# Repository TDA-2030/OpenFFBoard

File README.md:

# OpenFFBoard-ESP32S2 + VESC

这里将介绍使用 ESP32-S2/S3 版本的 OpenFFBoard 搭配自制 VESC 驱动器使用的一个低成本实现直驱力反馈方向盘方案。[OpenffBoard](https://github.com/Ultrawipf/OpenFFBoard) 是一个开源的力反馈方向盘的项目，整个项目硬件分为 `控制板` 和 `电机驱动板` 两个部分，这里对两个部分都进行了低成本方向的修改。

## 文件结构

```
├── LICENSE                <- 开源协议 >
├── Simple-BLDC            <- 电机驱动板 >
├── openffboard-esp32s2    <- OpenFFBoard 主控板 >
├── Structural_parts       <- 一些可能有帮助的结构件>
└── README.md              <- 此文件 >
```

## OpenFFBoard-ESP32S2 控制板

原项目控制板是 STM32F4 做主控，这里将主控换成了[乐鑫](https://www.espressif.com/zh-hans)的 ESP32-S2/S3 芯片，成本得到极大的降低，同时提供了 WiFi 的连接能力（虽然现在并没有用上）。硬件开源资料见 [openffboard-esp32s2](./openffboard-esp32s2)

> V1.1 版本的硬件支持 ESP32-S2 和 ESP32-S3 二选一焊接，下文统称为 ESP32

和原项目相比，ESP32 不能提供足够多的 GPIO ，所以按键输入和模拟输入通道数均从原来的 8 通道精简到了 4 通道。详细信息见原理图 [esp32s2-openffb.pdf](openffboard-esp32s2/esp32s2-openffb.pdf)。
ESP32 控制板的源码已提交 Pull Request 到原项目，支持的功能以及进度见 [PR](https://github.com/Ultrawipf/OpenFFBoard/pull/46)。

### 控制板固件烧录

参见[快速下载固件指南](https://github.com/TDA-2030/OpenFFBoard/tree/feature/add_esp32s2/Firmware/Targets/ESP32SX#quick-download-firmware)

## 电机驱动板

为了造福广大劳动人民，针对原项目的电机驱动我也进行了低成本的改造，原项目是采用了比较贵的 TMC4761 专用 FOC 控制芯片，我将著名的开源电调 [VESC](https://vesc-project.com/) 进行了魔改，去掉了昂贵的 DRV8301 芯片，用多个芯片实现了这一个芯片的功能。集成度下降了，但是价格更友好。魔改后的 VESC 我叫它 `Simple-BLDC` 。关于电机驱动板的更多信息见 [Simple-BLDC](Simple-BLDC/README.md)

## 组装好的样子

## 测试工具

[WheelTest](./WheelTest.rar) 提供了一个测试力反馈功能是否正常的软件

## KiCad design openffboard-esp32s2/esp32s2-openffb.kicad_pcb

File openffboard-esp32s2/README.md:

## Preview image

## Known issues

The silk screen of the two buttons is wrong

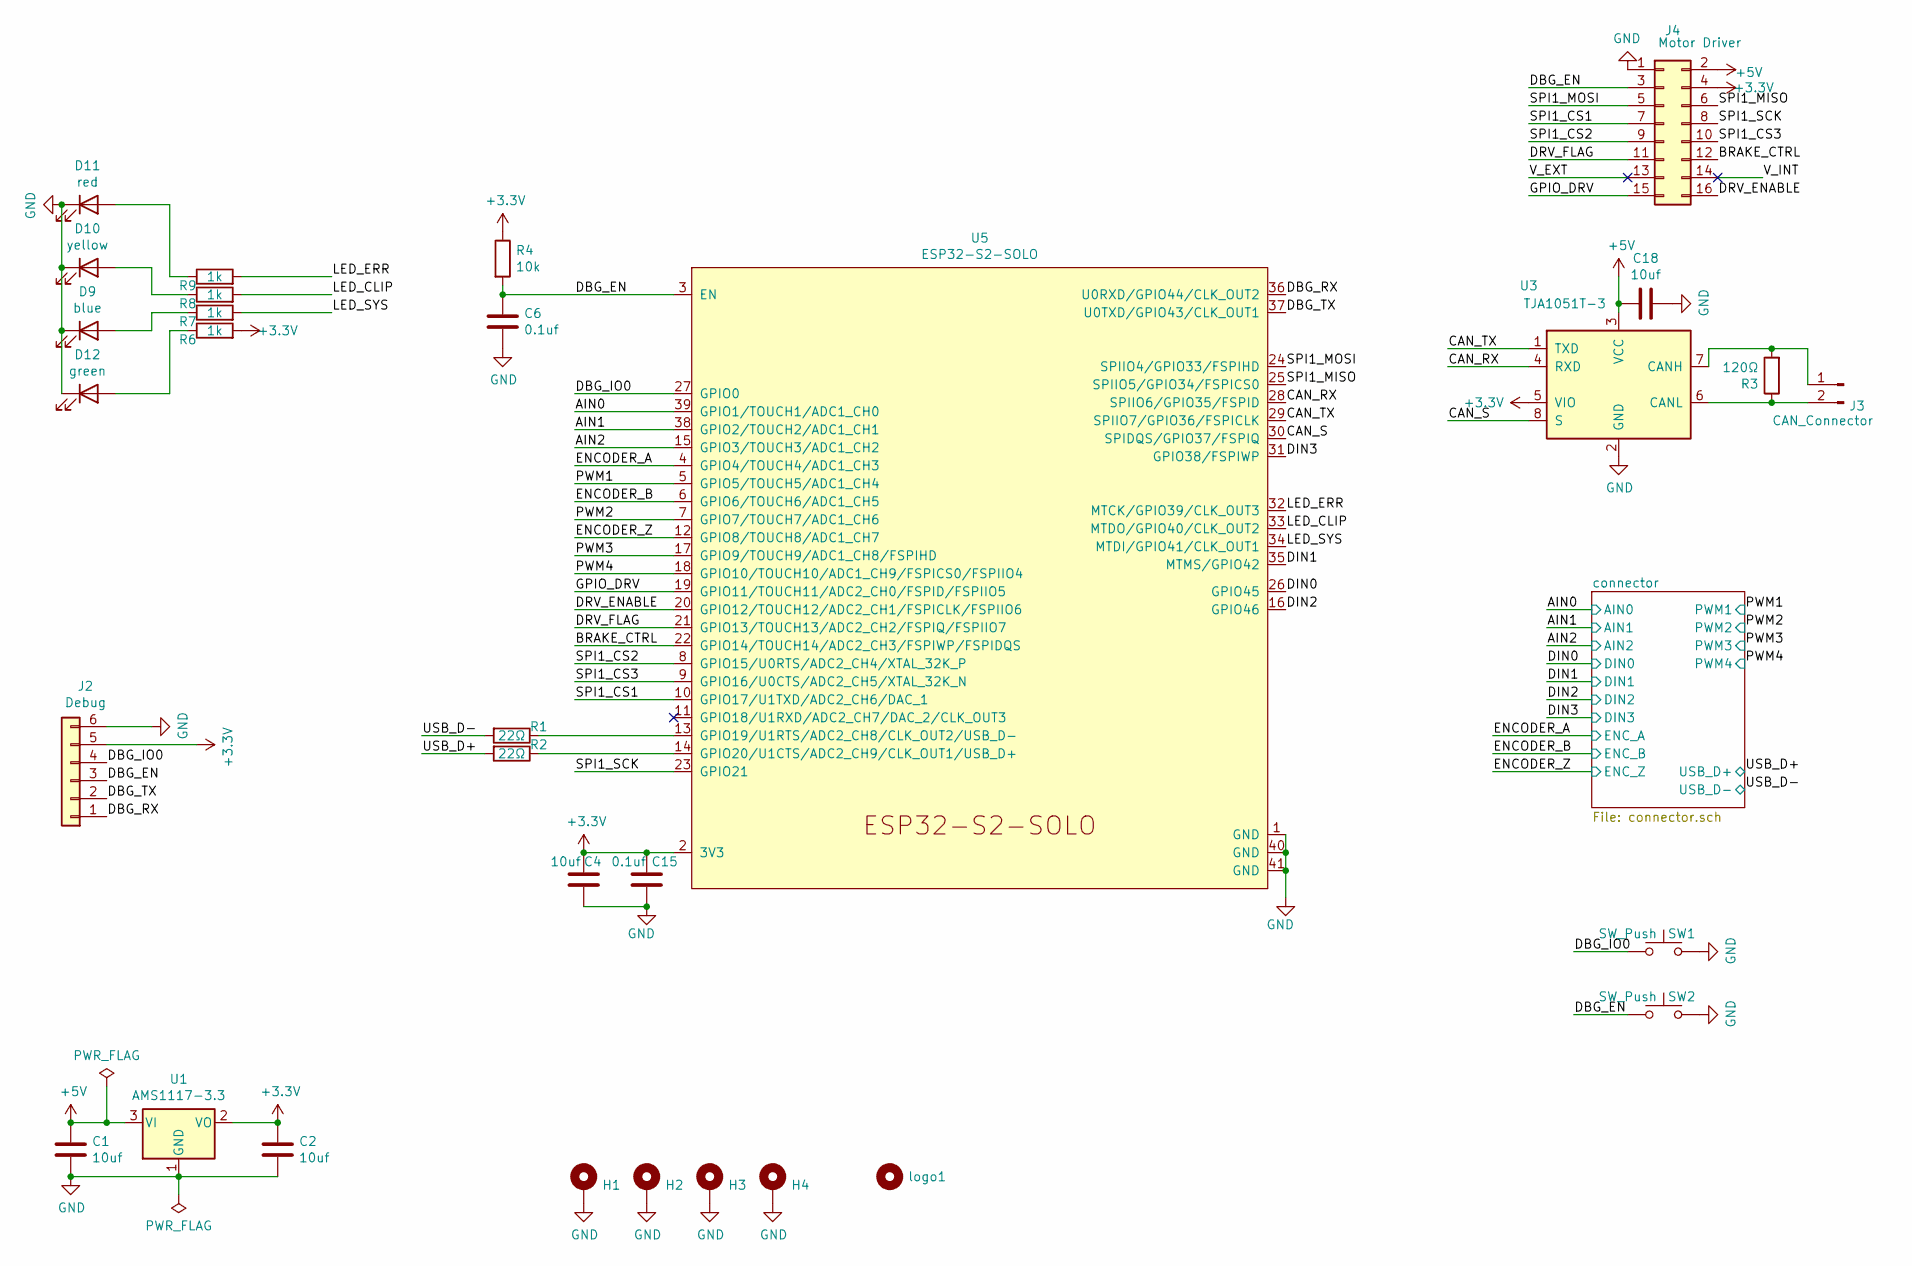
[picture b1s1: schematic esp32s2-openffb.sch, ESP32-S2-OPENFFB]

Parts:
C1, C2, C4, C18: 10uf; C_0603_1608Metric
C6, C15: 0.1uf; C_0402_1005Metric
D9: blue; LED_0603_1608Metric
D10: yellow; LED_0603_1608Metric
D11: red; LED_0603_1608Metric
D12: green; LED_0603_1608Metric
H1, H2, H3, H4: MountingHole_Pad; MountingHole_3.2mm_M3_Pad_Via
J2: Debug; PinHeader_1x06_P2.54mm_Vertical
J3: CAN_Connector; PinHeader_1x02_P2.54mm_Vertical
J4: Motor Driver; PinHeader_2x08_P2.54mm_Vertical
R1, R2: 22Ω; R_0402_1005Metric
R3: 120Ω; R_0603_1608Metric
R4: 10k; R_0402_1005Metric
R6, R7, R8, R9: 1k; R_0402_1005Metric
SW1, SW2: SW_Push; SW_SPST_EVPBF
U1: AMS1117-3.3; SOT-223-3_TabPin2
U3: TJA1051T-3; SOIC-8_3.9x4.9mm_P1.27mm
U5: ESP32-S2-SOLO
logo1: logo; OSHW-Logo2_9.8x8mm_SilkScreen

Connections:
+3V3: C2.2, C4.1, C15.1, J2.5, J4.4, R4.1, R6.2, U1.2 (VO), U3.5 (VIO), U5.2 (3V3); also elsewhere on the board
+5V: C1.2, C18.2, J4.2, U1.3 (VI), U3.3 (VCC); also elsewhere on the board
/AIN0: U5.39 (GPIO1/TOUCH1/ADC1_CH0); also elsewhere on the board
/AIN1: U5.38 (GPIO2/TOUCH2/ADC1_CH1); also elsewhere on the board
/AIN2: U5.15 (GPIO3/TOUCH3/ADC1_CH2); also elsewhere on the board
/BRAKE_CTRL: J4.12, U5.22 (GPIO14/TOUCH14/ADC2_CH3/FSPIWP/FSPIDQS)
/CAN_RX: U3.4 (RXD), U5.28 (SPIIO6/GPIO35/FSPID)
/CAN_S: U3.8 (S), U5.30 (SPIDQS/GPIO37/FSPIQ)
/CAN_TX: U3.1 (TXD), U5.29 (SPIIO7/GPIO36/FSPICLK)
/DBG_EN: C6.1, J2.3, J4.3, R4.2, SW2.1, U5.3 (EN)
/DBG_IO0: J2.4, SW1.1, U5.27 (GPIO0)
/DBG_RX: J2.1, U5.36 (U0RXD/GPIO44/CLK_OUT2)
/DBG_TX: J2.2, U5.37 (U0TXD/GPIO43/CLK_OUT1)
/DIN0: U5.26 (GPIO45); also elsewhere on the board
/DIN1: U5.35 (MTMS/GPIO42); also elsewhere on the board
/DIN2: U5.16 (GPIO46); also elsewhere on the board
/DIN3: U5.31 (GPIO38/FSPIWP); also elsewhere on the board
/DRV_ENABLE: J4.16, U5.20 (GPIO12/TOUCH12/ADC2_CH1/FSPICLK/FSPIIO6)
/DRV_FLAG: J4.11, U5.21 (GPIO13/TOUCH13/ADC2_CH2/FSPIQ/FSPIIO7)
/ENCODER_A: U5.4 (GPIO4/TOUCH4/ADC1_CH3); also elsewhere on the board
/ENCODER_B: U5.6 (GPIO6/TOUCH6/ADC1_CH5); also elsewhere on the board
/ENCODER_Z: U5.12 (GPIO8/TOUCH8/ADC1_CH7); also elsewhere on the board
/GPIO_DRV: J4.15, U5.19 (GPIO11/TOUCH11/ADC2_CH0/FSPID/FSPIIO5)
/LED_CLIP: R8.2, U5.33 (MTDO/GPIO40/CLK_OUT2)
/LED_ERR: R9.2, U5.32 (MTCK/GPIO39/CLK_OUT3)
/LED_SYS: R7.2, U5.34 (MTDI/GPIO41/CLK_OUT1)
/PWM1: U5.5 (GPIO5/TOUCH5/ADC1_CH4); also elsewhere on the board
/PWM2: U5.7 (GPIO7/TOUCH7/ADC1_CH6); also elsewhere on the board
/PWM3: U5.17 (GPIO9/TOUCH9/ADC1_CH8/FSPIHD); also elsewhere on the board
/PWM4: U5.18 (GPIO10/TOUCH10/ADC1_CH9/FSPICS0/FSPIIO4); also elsewhere on the board
/SPI1_CS1: J4.7, U5.10 (GPIO17/U1TXD/ADC2_CH6/DAC_1)
/SPI1_CS2: J4.9, U5.8 (GPIO15/U0RTS/ADC2_CH4/XTAL_32K_P)
/SPI1_CS3: J4.10, U5.9 (GPIO16/U0CTS/ADC2_CH5/XTAL_32K_N)
/SPI1_MISO: J4.6, U5.25 (SPIIO5/GPIO34/FSPICS0)
/SPI1_MOSI: J4.5, U5.24 (SPIIO4/GPIO33/FSPIHD)
/SPI1_SCK: J4.8, U5.23 (GPIO21)
/USB_D+: R2.2; also elsewhere on the board
/USB_D-: R1.2; also elsewhere on the board
GND: C1.1, C2.1, C4.2, C6.2, C15.2, C18.1, D9.1 (K), D10.1 (K), D11.1 (K), D12.1 (K), H1.1, H2.1, H3.1, H4.1, J2.6, J4.1, SW1.2, SW2.2, U1.1 (GND), U3.2 (GND), U5.1 (GND), U5.40 (GND), U5.41 (GND); also elsewhere on the board
unnamed: D9.2 (A), R7.1
unnamed: D10.2 (A), R8.1
unnamed: D11.2 (A), R9.1
unnamed: D12.2 (A), R6.1
unnamed: J3.1, R3.2, U3.7 (CANH)
unnamed: J3.2, R3.1, U3.6 (CANL)
unnamed: R1.1, U5.13 (GPIO19/U1RTS/ADC2_CH8/CLK_OUT2/USB_D-)
unnamed: R2.1, U5.14 (GPIO20/U1CTS/ADC2_CH9/CLK_OUT1/USB_D+)

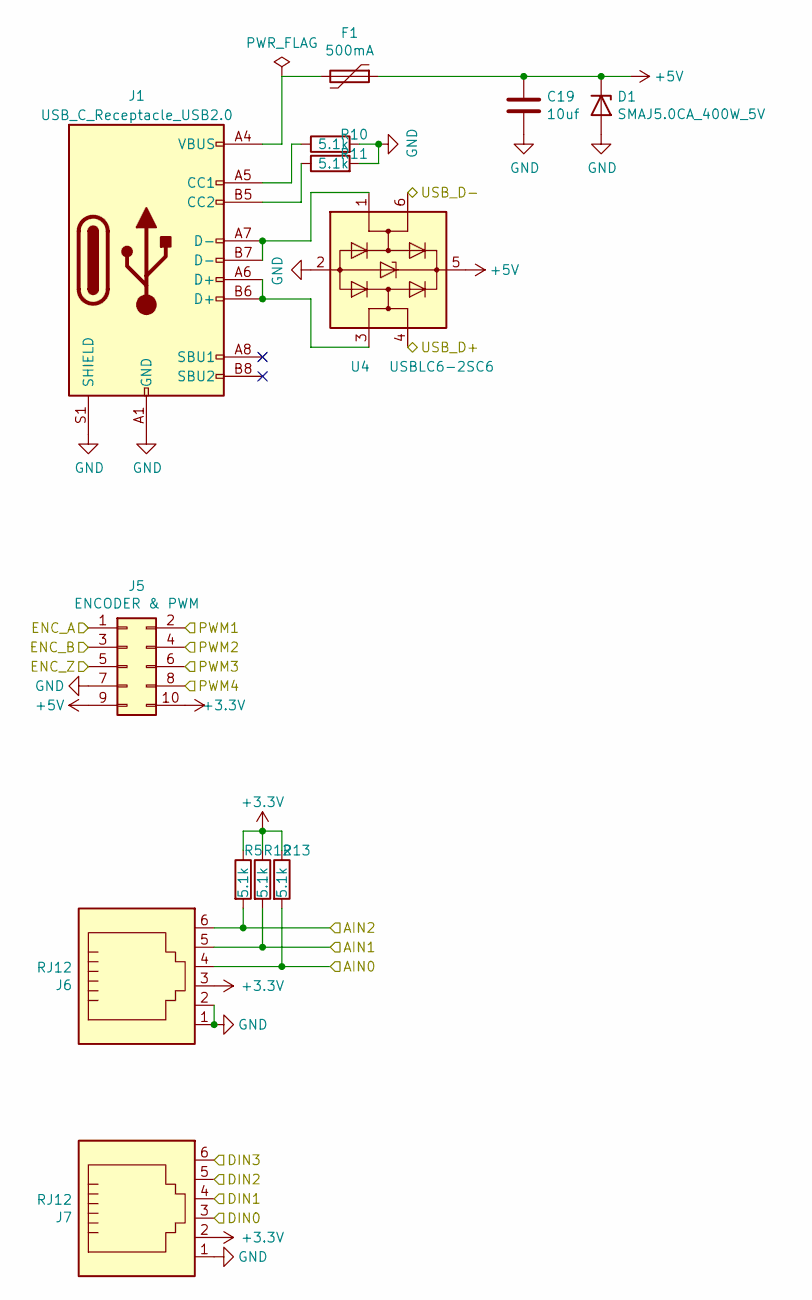
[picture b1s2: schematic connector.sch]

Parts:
C19: 10uf; C_0603_1608Metric
D1: SMAJ5.0CA_400W_5V; D_SMA
F1: 500mA; Fuse_0805_2012Metric
J1: USB_C_Receptacle_USB2.0; USB_C_Receptacle_Palconn_UTC16-G
J5: ENCODER & PWM; PinHeader_2x05_P2.54mm_Vertical
J6, J7: RJ12; RJ25_Wayconn_MJEA-660X1_Horizontal
R5, R10, R11, R12, R13: 5.1k; R_0402_1005Metric
U4: USBLC6-2SC6; SOT-23-6

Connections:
+3V3: J5.10, J6.3, J7.2, R5.1, R12.1, R13.1; also elsewhere on the board
+5V: C19.2, D1.1 (A1), F1.1, J5.9, U4.5 (VBUS); also elsewhere on the board
/AIN0: J6.4, R13.2; also elsewhere on the board
/AIN1: J6.5, R12.2; also elsewhere on the board
/AIN2: J6.6, R5.2; also elsewhere on the board
/DIN0: J7.3; also elsewhere on the board
/DIN1: J7.4; also elsewhere on the board
/DIN2: J7.5; also elsewhere on the board
/DIN3: J7.6; also elsewhere on the board
/ENCODER_A: J5.1; also elsewhere on the board
/ENCODER_B: J5.3; also elsewhere on the board
/ENCODER_Z: J5.5; also elsewhere on the board
/PWM1: J5.2; also elsewhere on the board
/PWM2: J5.4; also elsewhere on the board
/PWM3: J5.6; also elsewhere on the board
/PWM4: J5.8; also elsewhere on the board
/USB_D+: U4.4 (I/O2); also elsewhere on the board
/USB_D-: U4.6 (I/O1); also elsewhere on the board
GND: C19.1, D1.2 (A2), J1.A1 (GND), J1.A12 (GND), J1.B1 (GND), J1.B12 (GND), J1.S1 (SHIELD), J5.7, J6.1, J6.2, J7.1, R10.2, R11.2, U4.2 (GND); also elsewhere on the board
unnamed: F1.2, J1.A4 (VBUS), J1.A9 (VBUS), J1.B4 (VBUS), J1.B9 (VBUS)
unnamed: J1.A5 (CC1), R10.1
unnamed: J1.A6 (D+), J1.B6 (D+), U4.3 (I/O2)
unnamed: J1.A7 (D-), J1.B7 (D-), U4.1 (I/O1)
unnamed: J1.B5 (CC2), R11.1

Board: 2 copper layers, 44 parts (0 on the bottom side), 52 nets, no tracks yet.

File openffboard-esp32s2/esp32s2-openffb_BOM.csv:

"Comment","Description","Designator","Footprint","LibRef","Pins","Quantity","PartNumber","url",
"10uf","desc","C1,C2,C3,C4,C19,","C_0603_1608Metric","libref","2","5","","",
"0.1uf","desc","C6,C15,","C_0402_1005Metric","libref","2","2","","",
"SMAJ5.0CA_400W_5V","desc","D1,","D_SMA","libref","2","1","","",
"blue","desc","D9,","LED_0603_1608Metric","libref","2","1","","",
"yellow","desc","D10,","LED_0603_1608Metric","libref","2","1","","",
"red","desc","D11,","LED_0603_1608Metric","libref","2","1","","",
"green","desc","D12,","LED_0603_1608Metric","libref","2","1","","",
"500mA","desc","F1,","Fuse_0805_2012Metric","libref","2","1","","",
"22Ω","desc","R1,R2,","R_0402_1005Metric","libref","2","2","","",
"10k","desc","R4,","R_0402_1005Metric","libref","2","1","","",
"5.1k","desc","R5,R10,R11,R12,R13,","R_0402_1005Metric","libref","2","5","","",
"1k","desc","R6,R7,R8,R9,","R_0402_1005Metric","libref","2","4","","",
"120Ω","desc","R15,","R_0603_1608Metric","libref","2","1","","",
"AMS1117-3.3","desc","U1,","SOT-223-3_TabPin2","libref","4","1","","",
"ESP32-S3-WROOM-1","desc","U2,","ESP32-S3-WROOM-1","libref","49","1","","",
"TJA1051T-3","desc","U3,","SOIC-8_3.9x4.9mm_P1.27mm","libref","8","1","","",
"USBLC6-2SC6","desc","U4,","SOT-23-6","libref","6","1","","",
"ESP32-S2-SOLO","desc","U5,","ESP32-S2-SOLO","libref","49","1","","",
"SW_Push","desc","SW1,SW2,","SW_SPST_EVPBF","libref","4","2","","",
"logo","desc","logo1,","OSHW-Logo2_9.8x8mm_SilkScreen","libref","0","1","","",
"Through Hole Items ",
"MountingHole_Pad","desc","H1,H2,H3,H4,","MountingHole_3.2mm_M3_Pad_Via","libref","9","4","","",
"USB_C_Receptacle_USB2.0","desc","J1,","USB_C_Receptacle_Palconn_UTC16-G","libref","22","1","","",
"Debug","desc","J2,","PinHeader_1x06_P2.54mm_Vertical","libref","6","1","","",
"CAN_Connector","desc","J3,","PinHeader_1x02_P2.54mm_Vertical","libref","2","1","","",
"Motor Driver","desc","J4,","PinHeader_2x08_P2.54mm_Vertical","libref","16","1","","",
"ENCODER & PWM","desc","J5,","PinHeader_2x05_P2.54mm_Vertical","libref","10","1","","",
"RJ12","desc","J6,J7,","RJ25_Wayconn_MJEA-660X1_Horizontal","libref","8","2","","",

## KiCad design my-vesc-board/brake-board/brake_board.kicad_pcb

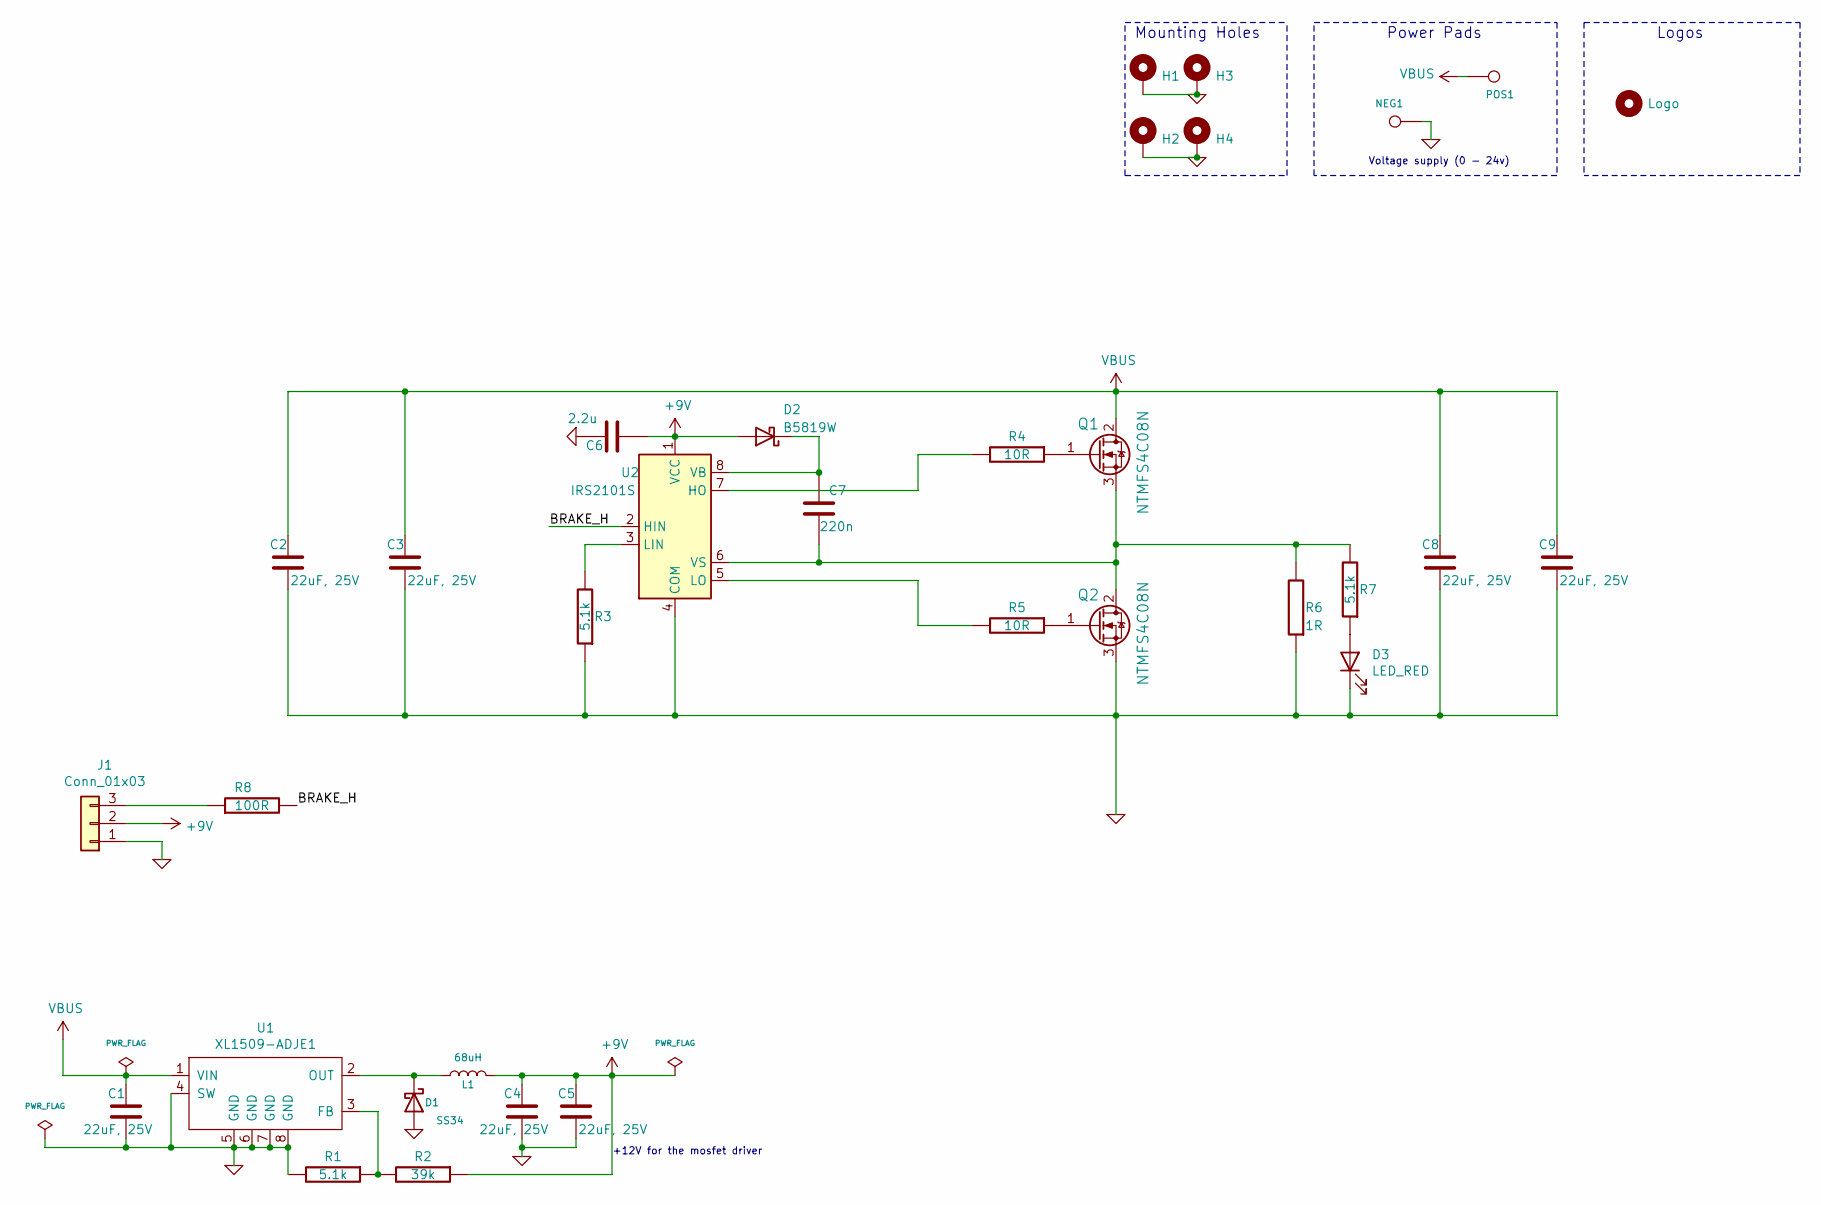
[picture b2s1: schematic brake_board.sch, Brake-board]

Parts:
C1, C2, C3, C4, C5, C8, C9: 22uF, 25V; C_1206_3216Metric
C6: 2.2u; C_0402_1005Metric
C7: 220n; C_0603_1608Metric
D1: SS34; D_SMA
D2: B5819W; D_SOD-123
D3: LED_RED; LED_0603_1608Metric_Castellated
H1, H2, H3, H4: MountingHole_Pad; MountingHole_3.2mm_M3_Pad_Via
H6: Logo; simple-bldc-logo1
J1: Conn_01x03; PinHeader_1x03_P2.54mm_Vertical
L1: 68uH; L_Taiyo-Yuden_NR-60xx_HandSoldering
NEG1: MOTOR3; 1pin_2mm
POS1: POS; 1pin_2mm
Q1, Q2: NTMFS4C08N; DFN5_5x6_1.27P_(SO-8FL)
R1, R3, R7: 5.1k; R_0402_1005Metric
R2: 39k; R_0402_1005Metric
R4, R5: 10R; R_0402_1005Metric
R6: 1R; R_Axial_Power_L48.0mm_W12.5mm_P55.88mm
R8: 100R; R_0402_1005Metric
U1: XL1509-ADJE1; SOIC-8_3.9x4.9mm_P1.27mm
U2: IRS2101S; SOIC-8_3.9x4.9mm_P1.27mm

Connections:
+9V: C4.2, C5.2, C6.1, D2.2 (A), J1.2, L1.2, R2.1, U2.1 (VCC)
/BRAKE_H: R8.2, U2.2 (HIN)
GND: C1.1, C2.1, C3.1, C4.1, C5.1, C6.2, C8.1, C9.1, D1.2 (A), D3.1 (K), H1.1, H2.1, H3.1, H4.1, J1.1, NEG1.1, Q2.3 (S), R1.2, R3.1, R6.1, U1.4 (SW), U1.5 (GND), U1.6 (GND), U1.7 (GND), U1.8 (GND), U2.4 (COM)
unnamed: C7.1, D2.1 (K), U2.8 (VB)
unnamed: C7.2, Q1.3 (S), Q2.2 (D), R6.2, R7.2, U2.6 (VS)
unnamed: D1.1 (K), L1.1, U1.2 (OUT)
unnamed: D3.2 (A), R7.1
unnamed: J1.3, R8.1
unnamed: Q1.1 (G), R4.1
unnamed: Q2.1 (G), R5.1
unnamed: R1.1, R2.2, U1.3 (FB)
unnamed: R3.2, U2.3 (LIN)
unnamed: R4.2, U2.7 (HO)
unnamed: R5.2, U2.5 (LO)
VBUS: C1.2, C2.2, C3.2, C8.2, C9.2, POS1.1, Q1.2 (D), U1.1 (VIN)

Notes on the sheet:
+12V for the mosfet driver
Voltage supply (0 - 24v)
Mounting Holes
Power Pads
Logos

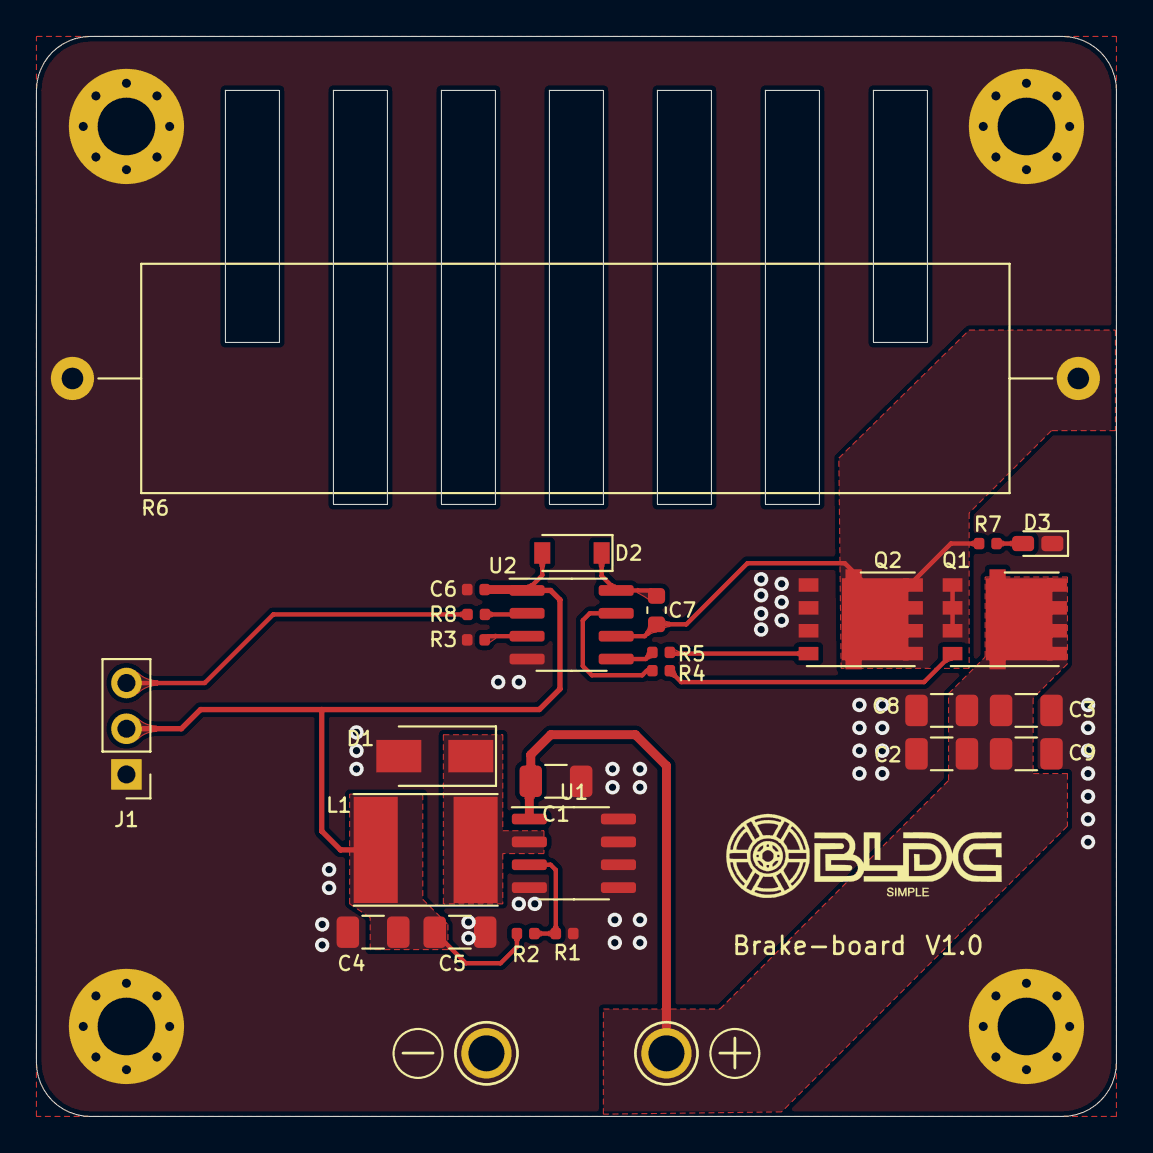
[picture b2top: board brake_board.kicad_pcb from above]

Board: 2 copper layers, 60.0 x 60.0 mm, 33 parts (0 on the bottom side), 15 nets.

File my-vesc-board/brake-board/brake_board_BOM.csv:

"Comment","Description","Designator","Footprint","LibRef","Pins","Quantity","PartNumber","url",
"22uF, 25V","desc","C1,C2,C3,C4,C5,C8,C9,","C_1206_3216Metric","libref","2","7","","",
"2.2u","desc","C6,","C_0402_1005Metric","libref","2","1","","",
"220n","desc","C7,","C_0603_1608Metric","libref","2","1","","",
"SS34","desc","D1,","D_SMA","libref","2","1","","",
"B5819W","desc","D2,","D_SOD-123","libref","2","1","","",
"LED_RED","desc","D3,","LED_0603_1608Metric_Castellated","libref","2","1","","",
"Logo","desc","H6,","simple-bldc-logo1","libref","0","1","","",
"68uH","desc","L1,","L_Taiyo-Yuden_NR-60xx_HandSoldering","libref","2","1","","",
"NTMFS4C08N","desc","Q1,Q2,","DFN5_5x6_1.27P_(SO-8FL)","libref","10","2","","",
"5.1k","desc","R1,R3,R7,","R_0402_1005Metric","libref","2","3","","",
"39k","desc","R2,","R_0402_1005Metric","libref","2","1","","",
"10R","desc","R4,R5,","R_0402_1005Metric","libref","2","2","","",
"100R","desc","R8,","R_0402_1005Metric","libref","2","1","","",
"XL1509-ADJE1","desc","U1,","SOIC-8_3.9x4.9mm_P1.27mm","libref","8","1","","",
"IRS2101S","desc","U2,","SOIC-8_3.9x4.9mm_P1.27mm","libref","8","1","","",
"Through Hole Items ",
"MountingHole_Pad","desc","H1,H2,H3,H4,","MountingHole_3.2mm_M3_Pad_Via","libref","9","4","","",
"Conn_01x03","desc","J1,","PinHeader_1x03_P2.54mm_Vertical","libref","3","1","","",
"1R","desc","R6,","R_Axial_Power_L48.0mm_W12.5mm_P55.88mm","libref","2","1","","",
"MOTOR3","desc","NEG1,","1pin_2mm","libref","1","1","","",
"POS","desc","POS1,","1pin_2mm","libref","1","1","","",

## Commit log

2022-01-10 v1.0
2022-04-30 add vesc and docs
2022-04-30 v1.1
2022-09-02 add structual parts
2022-09-05 update simple-bldc board
2024-07-15 Structural_parts: add ver4
